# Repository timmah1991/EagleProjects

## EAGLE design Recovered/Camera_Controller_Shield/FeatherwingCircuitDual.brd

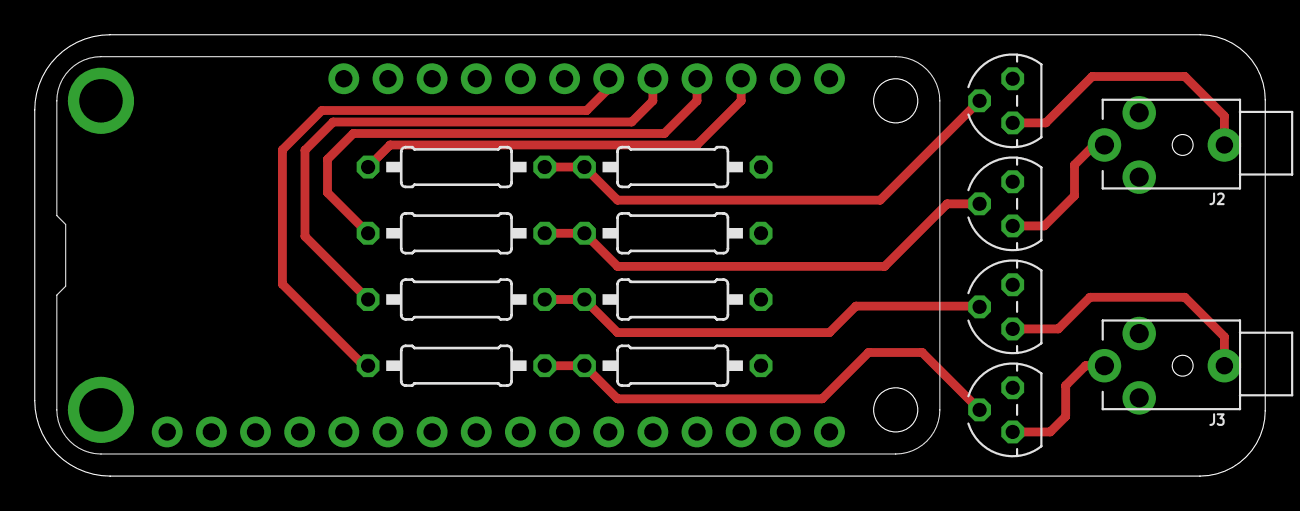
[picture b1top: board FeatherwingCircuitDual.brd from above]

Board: 2 copper layers, 70.8 x 25.4 mm, 15 parts (0 on the bottom side), 13 nets.

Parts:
J2, J3: STEREOJACK2.5MM_STEREOJACK2.5MM
MS1: FEATHERWING_NODIM; FEATHERWING_DIM
Q1, Q2, Q3, Q4: BC547B; TO92
R1, R2, R3, R4, R5, R6, R7, R8: 10K; PR-D2.3XL6.5MM

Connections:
GND: J2.RING1, J3.RING1, MS1.4, Q1.1, Q2.1, Q3.1, Q4.1, R3.1, R4.1, R7.1, R8.1
unnamed: Q1.2, R1.2, R3.2
unnamed: Q2.2, R2.2, R4.2
unnamed: J2.TIP, Q1.3
unnamed: J2.SHIELD, Q2.3
unnamed: Q3.2, R5.2, R7.2
unnamed: MS1.19, R2.1
unnamed: MS1.20, R1.1
unnamed: Q4.2, R6.2, R8.2
unnamed: J3.TIP, Q3.3
unnamed: J3.SHIELD, Q4.3
unnamed: MS1.21, R6.1
unnamed: MS1.22, R5.1

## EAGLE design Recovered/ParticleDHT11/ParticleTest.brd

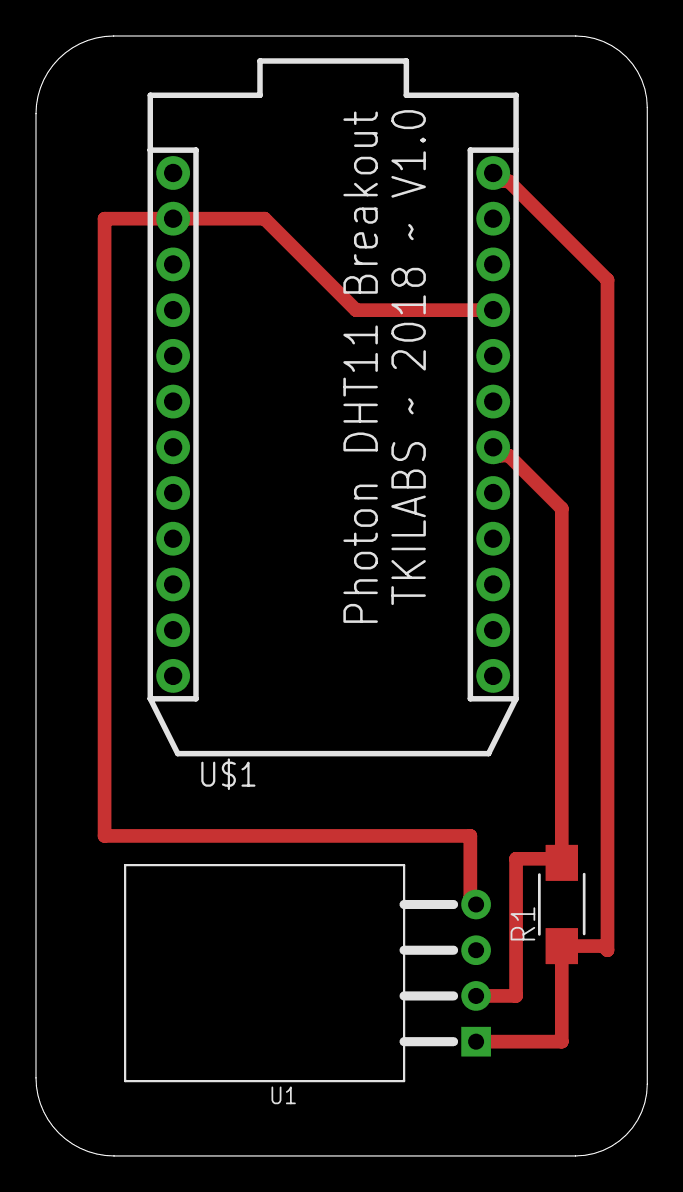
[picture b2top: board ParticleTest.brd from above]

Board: 2 copper layers, 34.0 x 62.2 mm, 3 parts (0 on the bottom side), 3 nets.

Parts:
R1: R2010W
U1: DHT11; SNR4-2.54-15.5X12.0X5.5MM
U$1: PHOTON_WITH_HEADERS; PHOTON

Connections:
GND: U1.4, U$1.2, U$1.21
unnamed: R1.2, U1.2, U$1.18
VDD: R1.1, U1.1, U$1.24

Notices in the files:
parts and their libraries:
SparkFun-Connectors: Licensing: Creative Commons ShareAlike 4.0 International - https://creativecommons.org/licenses/by-sa/4.0
Particle-Devices: Licensing: Designed by Particle.
